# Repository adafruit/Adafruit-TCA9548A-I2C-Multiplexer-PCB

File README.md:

## Adafruit TCA9548A I2C Multiplexer PCB
<a href="http://www.adafruit.com/products/2717"><br/>
Click here to purchase one from the Adafruit shop</a>

You just found the perfect I2C sensor, and you want to wire up two or three or more of them to your Arduino when you realize "Uh oh, this chip has a fixed I2C address, and from what I know about I2C, you cannot have two devices with the same address on the same SDA/SCL pins!" Are you out of luck? You would be, if you didn't have this ultra-cool TCA9548A 1-to-8 I2C multiplexer!

Finally, a way to get up to 8 same-address I2C devices hooked up to one microcontroller - this multiplexer acts as a gatekeeper, shuttling the commands to the selected set of I2C pins with your command.

Using it is fairly straight-forward: the multiplexer itself is on I2C address 0x70 (but can be adjusted from 0x70 to 0x77) and you simply write a single byte with the desired multiplexed output number to that port, and bam - any future I2C packets will get sent to that port. In theory, you could have 8 of these multiplexers on each of 0x70-0x77 addresses in order to control 64 of the same-I2C-addressed-part.

PCB files for the Adafruit TCA9548A I2C Multiplexer. The format is EagleCAD schematic and board layout
- https://www.adafruit.com/products/2717

### License

Adafruit invests time and resources providing this open source design, please support Adafruit and open-source hardware by purchasing products from [Adafruit](https://www.adafruit.com)!

All text above must be included in any redistribution

Designed by Limor Fried/Ladyada for Adafruit Industries.
Creative Commons Attribution/Share-Alike, all text above must be included in any redistribution. 
See license.txt for additional information.

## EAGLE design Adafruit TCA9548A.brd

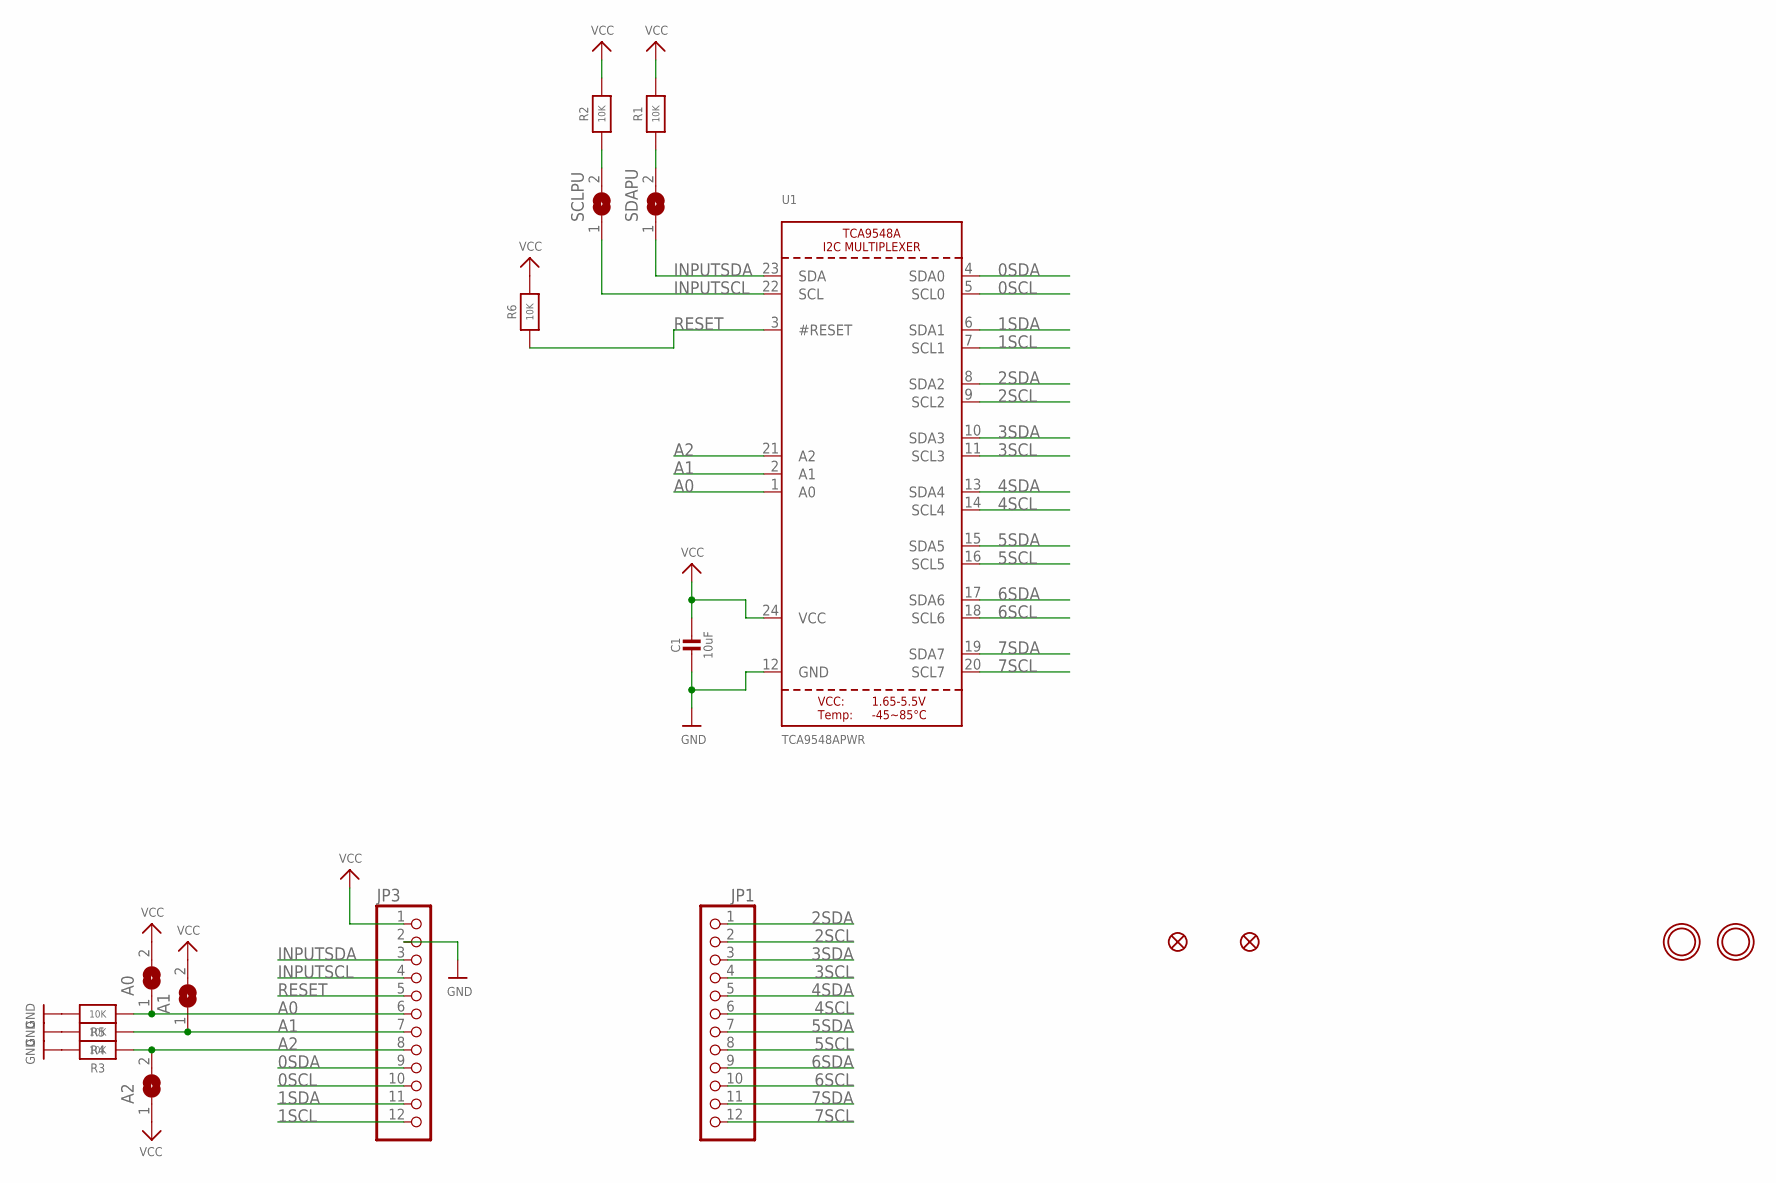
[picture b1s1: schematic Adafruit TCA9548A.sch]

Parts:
A0, A1, A2: SOLDERJUMPER; SOLDERJUMPER_ARROW_NOPASTE
C1: 10uF; 0805-NO
FID1, FID3: FIDUCIAL""; FIDUCIAL_1MM
JP1, JP3: HEADER-1X12; 1X12_ROUND
R1, R2, R3, R4, R5: 10K; 0805-NO
R6: 10K; _0805MP
SCLPU: SOLDERJUMPERCLOSED; SOLDERJUMPER_CLOSEDWIRE
SDAPU: SOLDERJUMPERCLOSED; SOLDERJUMPER_CLOSEDWIRE
U1: TCA9548APWR; TSSOP24
U$4, U$5: MOUNTINGHOLE2.5; MOUNTINGHOLE_2.5_PLATED

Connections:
0SCL: JP3.10, U1.5 (SCL0)
0SDA: JP3.9, U1.4 (SDA0)
1SCL: JP3.12, U1.7 (SCL1)
1SDA: JP3.11, U1.6 (SDA1)
2SCL: JP1.2, U1.9 (SCL2)
2SDA: JP1.1, U1.8 (SDA2)
3SCL: JP1.4, U1.11 (SCL3)
3SDA: JP1.3, U1.10 (SDA3)
4SCL: JP1.6, U1.14 (SCL4)
4SDA: JP1.5, U1.13 (SDA4)
5SCL: JP1.8, U1.16 (SCL5)
5SDA: JP1.7, U1.15 (SDA5)
6SCL: JP1.10, U1.18 (SCL6)
6SDA: JP1.9, U1.17 (SDA6)
7SCL: JP1.12, U1.20 (SCL7)
7SDA: JP1.11, U1.19 (SDA7)
A0: A0.1, JP3.6, R5.1, U1.1 (A0)
A1: A1.1, JP3.7, R4.1, U1.2 (A1)
A2: A2.2, JP3.8, R3.1, U1.21 (A2)
GND: C1.2, JP3.2, R3.2, R4.2, R5.2, U1.12 (GND)
INPUTSCL: JP3.4, SCLPU.1, U1.22 (SCL)
INPUTSDA: JP3.3, SDAPU.1, U1.23 (SDA)
unnamed: R2.1, SCLPU.2
unnamed: R1.1, SDAPU.2
RESET: JP3.5, R6.1, U1.3 (#RESET)
VCC: A0.2, A1.2, A2.1, C1.1, JP3.1, R1.2, R2.2, R6.2, U1.24 (VCC)

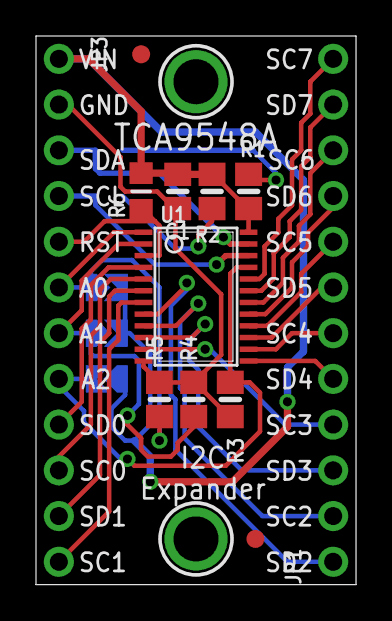
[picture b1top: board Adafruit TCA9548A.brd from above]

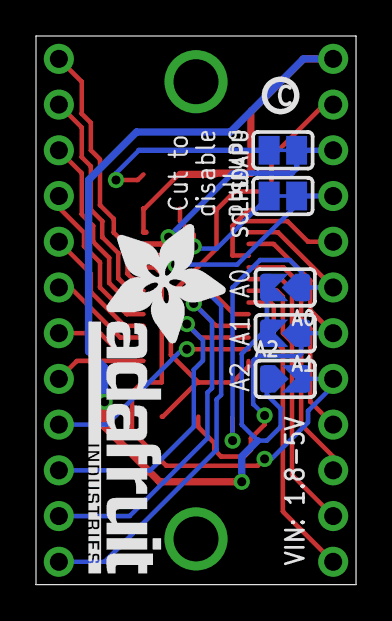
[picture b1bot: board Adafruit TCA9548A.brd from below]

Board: 2 copper layers, 17.8 x 30.5 mm, 21 parts (7 on the bottom side), 26 nets.

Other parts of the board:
U$6: PCBFEAT-REV-040
U$7: ADAFRUIT_TEXT_20MM

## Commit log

2016-09-21 init

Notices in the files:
parts and their libraries:
microbuilder: This work is placed in the public domain, and may be freely used for commercial and non-commercial work with the following conditions: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
